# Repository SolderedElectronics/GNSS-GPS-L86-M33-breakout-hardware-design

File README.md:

# GNSS GPS L86-M33 breakout Hardware Design

## About the Product

|  |
| :----------------------------------------------------------: |
| [Buy GNSS GPS L86-M33 breakout](https://www.solde.red/333201) |

Global Navigation Satellite Systems (GNSS), or as we all like to call it “GPS,” enable precise location determination on Earth. Thanks to this module, you can use GNSS for your project and employ the device for asset tracking or create a wearable device. The module is small, energy-efficient, highly effective, and easy to use thanks to its built-in antenna.

L86-M33 is a GNSS receiver, meaning it can receive signals from GPS, GLONASS, and Galileo constellations. Equipped with EASY (Embedded Assist System for self-generated orbit prediction) and AlwaysLocate technologies, the L86-M33 ensures fast and accurate positioning even in challenging environments. Its advanced internal logger, LOCUS, allows you to store your routes and location data.

In addition to the aforementioned L86-M33 module, which has an integrated antenna, our breakout board also has a connector for a CR1220 battery that is used as a backup for timekeeping and GPS data. The module can operate without a battery, but each time it will have to pull data from the satellites anew (cold start). If the integrated antenna is not sufficient, there is an IPX connector on the board for adding an external, stronger antenna. To easily access the pins of the module, the pins are exposed on the board for easy access.

---

## Repository Contents

This repository contains all design files for GNSS GPS L86-M33 breakout, organized as follows:

- **`CAD` folder**: Contains KiCAD design files, including:
  - Schematics
  - PCB layout
  - Panel PCB layout
  - Source 3D files in Fusion360, if any
  - All files are sorted by version with a detailed change log.
- **`OUTPUTS` folder**: Includes all production-ready files, such as:
  - Bill of Materials (BOM) and interactive BOM (iBOM)
  - PDF versions of schematics
  - 3D `.step` file of the board
  - 3D-printable models
  - Gerber files for PCB manufacturing
  - Image of the pinout of the board
  - Product image
  - Compliance, legal and generic sales documents

Refer to the `Change Log` in the CAD folder for details about updates between versions.

---

## Learn More About the Product

Beyond the repository, explore the following resources:

### Soldered Verify

The **Soldered Verify** system ensures every board you purchase from Soldered is fully functional. It also provides access to exclusive test data for your product. To get started, find the unique Soldered Verify ID on your product's packaging and enter the ID on the [Soldered Verify page](https://soldered.com/verify/) to access test results and additional product details.

### Soldered Community

Soldered Community is your go-to place for technical support. Our engineers track and answer all questions posted there, and it’s a great space for the maker community. Get answers to your questions and solutions for your challenges at [Soldered Community](https://soldered.com/community).

### solde.red

solde.red is an ultimate URL shortener and information hub. Access it by typing solde.red/ followed by your product SKU, e.g., [solde.red/333000](https://solde.red/333000), to find getting-started guides, datasheets, open-source hardware and software files, certifications, images, pinouts, and more. Read more about the shortener [here](https://solde.red/info/).

---

## Contributing

Contributions are welcome! Here’s how you can get involved:

- Submit pull requests to enhance the design or fix issues.
- Report bugs or problems by opening an issue.

We encourage community collaboration to make this product even better.

---

## About Soldered

[Soldered for Makers](https://soldered.com) specializes in designing and manufacturing electronic products tailored for enthusiasts, ranging from hobbyists to professionals. Our portfolio includes electronic boards, sensors, and actuators that are widely utilized in fields such as microelectronics, mechatronics, robotics, programming, and IoT. Every product we offer is designed in-house and built upon open-source hardware and software platforms. Proudly certified and manufactured within the European Union, our catalog likely includes the product you need for your project.

We complement these products with comprehensive tutorials and manuals, product descriptions, schematics, programming codes, and project examples. Our round-the-clock [customer and technical support](https://soldered.com/community) is available for all our products, irrespective of the sales channel. Soldered’s success and services reflect our maker community’s unwavering [trust](https://www.trustpilot.com/review/soldered.com), for which we are deeply grateful. Join our community and create using Soldered products.

---

## License

All Soldered open-source hardware (OSH) is under The TAPR Open Hardware License. Read more in the LICENSE file located in this repository.

**Disclaimer:**

No warranty - all designs in this repository are distributed in the hope that they will be useful, but without any warranty. They are provided "AS IS", therefore without warranty of any kind, either expressed or implied. The entire quality and performance of what you do with the contents of this repository are your responsibility. In no event Soldered Electronics will be liable for your damages, or losses, including any general, special, incidental, or consequential damage arising out of the use or inability to use the contents of this repository. 

---

## Have fun!

Thank you for your support from your fellow makers at Soldered Electronics.

Happy Making!

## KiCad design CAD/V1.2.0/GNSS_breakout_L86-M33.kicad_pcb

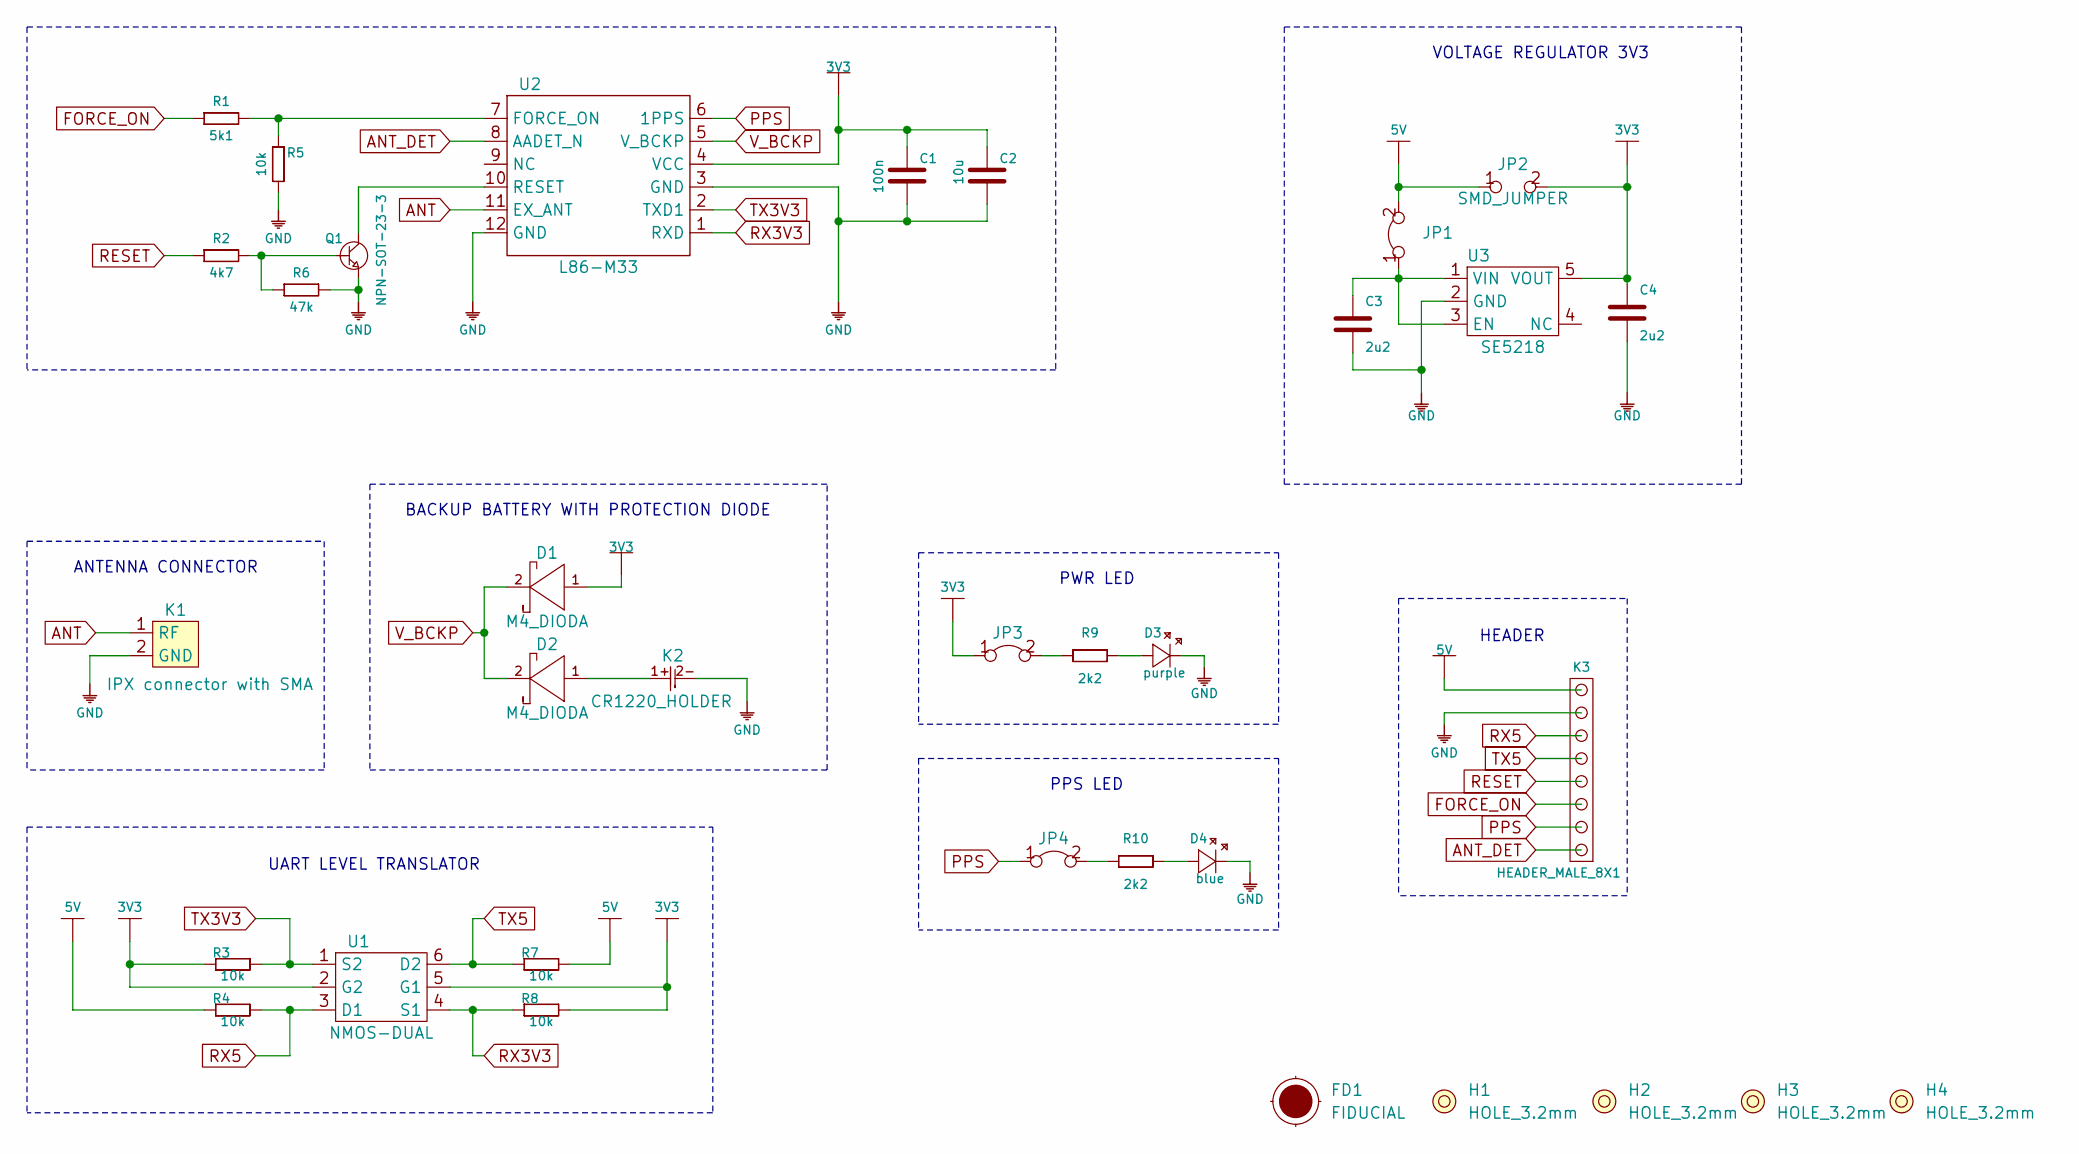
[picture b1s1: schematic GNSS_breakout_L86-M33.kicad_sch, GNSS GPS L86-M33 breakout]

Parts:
C1: 100n; 0603C
C2: 10u; 1206C
C3, C4: 2u2; 0603C
D1, D2: M4_DIODA
D3: purple; 0402LED
D4: blue; 0402LED
FD1: FIDUCIAL; FIDUCIAL_23
H1, H2, H3, H4: HOLE_3.2mm
JP1, JP3, JP4: SMD-JUMPER-CONNECTED_TRACE_SLODERMASK
JP2: SMD_JUMPER
K1: IPX connector with SMA
K2: CR1220_HOLDER
K3: HEADER_MALE_8X1
Q1: NPN-SOT-23-3; SOT-23-3
R1: 5k1; 0603R
R2: 4k7; 0603R
R3, R4, R5, R7, R8: 10k; 0603R
R6: 47k; 0603R
R9, R10: 2k2; 0402R
U1: NMOS-DUAL; SOT-363
U2: L86-M33
U3: SE5218; SOT-23-5

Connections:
3V3: C1.2, C2.2, C4.2, D1.1 (A), JP2.2, JP3.1, R3.1, R8.2, U1.2 (G2), U1.5 (G1), U2.4 (VCC), U3.5 (VOUT)
5V: JP1.2, JP2.1, K3.8, R4.1, R7.2
ANT: K1.1 (RF), U2.11 (EX_ANT)
ANT_DET: K3.1, U2.8 (AADET_N)
FORCE_ON: K3.3, R1.1
GND: C1.1, C2.1, C3.1, C4.1, D3.2 (K), D4.2 (K), K1.2 (GND), K2.2-, K3.7, Q1.2 (E), R5.2, R6.2, U2.3 (GND), U2.12 (GND), U3.2 (GND)
unnamed: C3.2, JP1.1, U3.1 (VIN), U3.3 (EN)
unnamed: D2.1 (A), K2.1+
unnamed: D3.1 (A), R9.2
unnamed: D4.1 (A), R10.2
unnamed: JP3.2, R9.1
unnamed: JP4.2, R10.1
unnamed: Q1.1 (B), R2.2, R6.1
unnamed: Q1.3 (C), U2.10 (RESET)
unnamed: R1.2, R5.1, U2.7 (FORCE_ON)
PPS: JP4.1, K3.2, U2.6 (1PPS)
RESET: K3.4, R2.1
RX3V3: R8.1, U1.4 (S1), U2.1 (RXD)
RX5: K3.6, R4.2, U1.3 (D1)
TX3V3: R3.2, U1.1 (S2), U2.2 (TXD1)
TX5: K3.5, R7.1, U1.6 (D2)
V_BCKP: D1.2 (K), D2.2 (K), U2.5 (V_BCKP)

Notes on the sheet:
ANTENNA CONNECTOR
PPS LED
VOLTAGE REGULATOR 3V3
BACKUP BATTERY WITH PROTECTION DIODE
UART LEVEL TRANSLATOR
PWR LED
HEADER

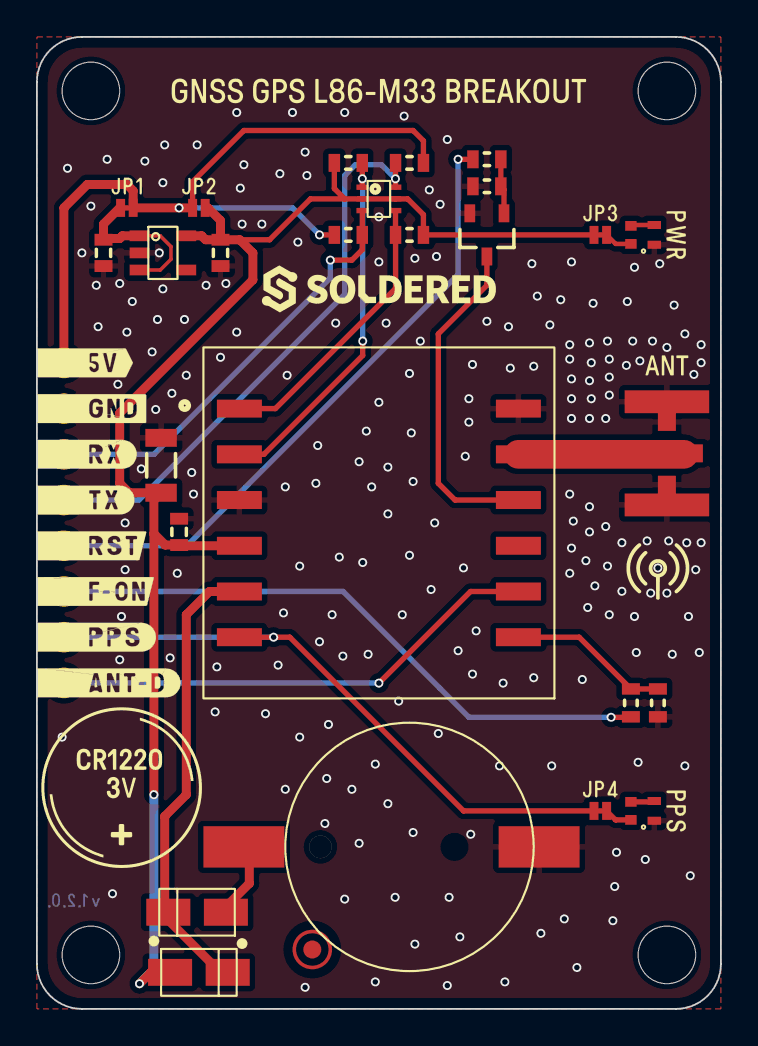
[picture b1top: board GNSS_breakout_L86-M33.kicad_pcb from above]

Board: 2 copper layers, 38.0 x 54.0 mm, 36 parts (0 on the bottom side), 22 nets.

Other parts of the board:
kibuzzard-62FB46FA: G***; kibuzzard-62FB46FA
kibuzzard-6391DAF4: G***; kibuzzard-6391DAF4

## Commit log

2022-08-06 Updating open source files.
2025-01-19 Delete OUTPUTS directory
    Oop
